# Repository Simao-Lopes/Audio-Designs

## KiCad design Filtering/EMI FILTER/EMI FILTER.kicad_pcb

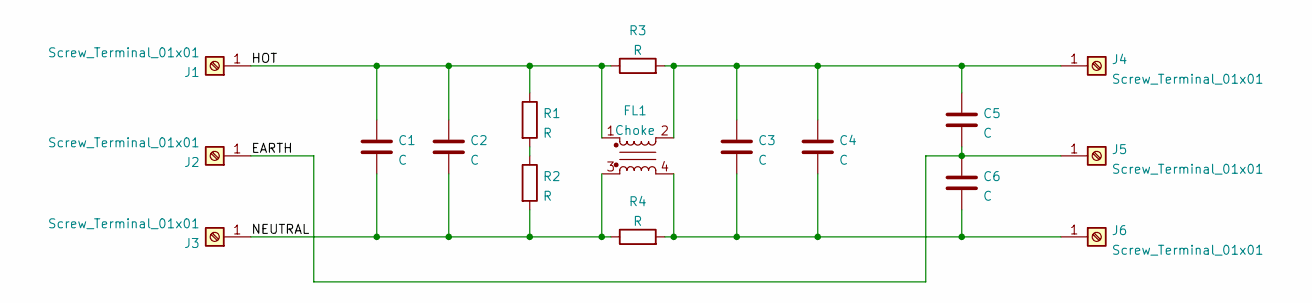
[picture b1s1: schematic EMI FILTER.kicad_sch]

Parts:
C1, C2, C3, C4: C; C_Rect_L31.5mm_W13.0mm_P27.50mm_MKS4
C5, C6: C; C_Rect_L13.0mm_W5.0mm_P10.00mm_FKS3_FKP3_MKS4
FL1: Choke; IND_CMT-8121
J1, J2, J3, J4, J5, J6: Screw_Terminal_01x01; M4_Screw_Terminal
R1, R2: R; R_Axial_DIN0207_L6.3mm_D2.5mm_P7.62mm_Horizontal
R3, R4: R; R_Axial_DIN0516_L15.5mm_D5.0mm_P20.32mm_Horizontal

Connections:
/EARTH: C5.2, C6.1, J2.1, J5.1
/HOT: C1.1, C2.1, FL1.1, J1.1, R1.1, R3.1; also elsewhere on the board
/NEUTRAL: C1.2, C2.2, FL1.3, J3.1, R2.2, R4.1; also elsewhere on the board
unnamed 3: C3.1, C4.1, C5.1, FL1.2, J4.1, R3.2; also elsewhere on the board
unnamed 4: C3.2, C4.2, C6.2, FL1.4, J6.1, R4.2; also elsewhere on the board
unnamed: R1.2, R2.1

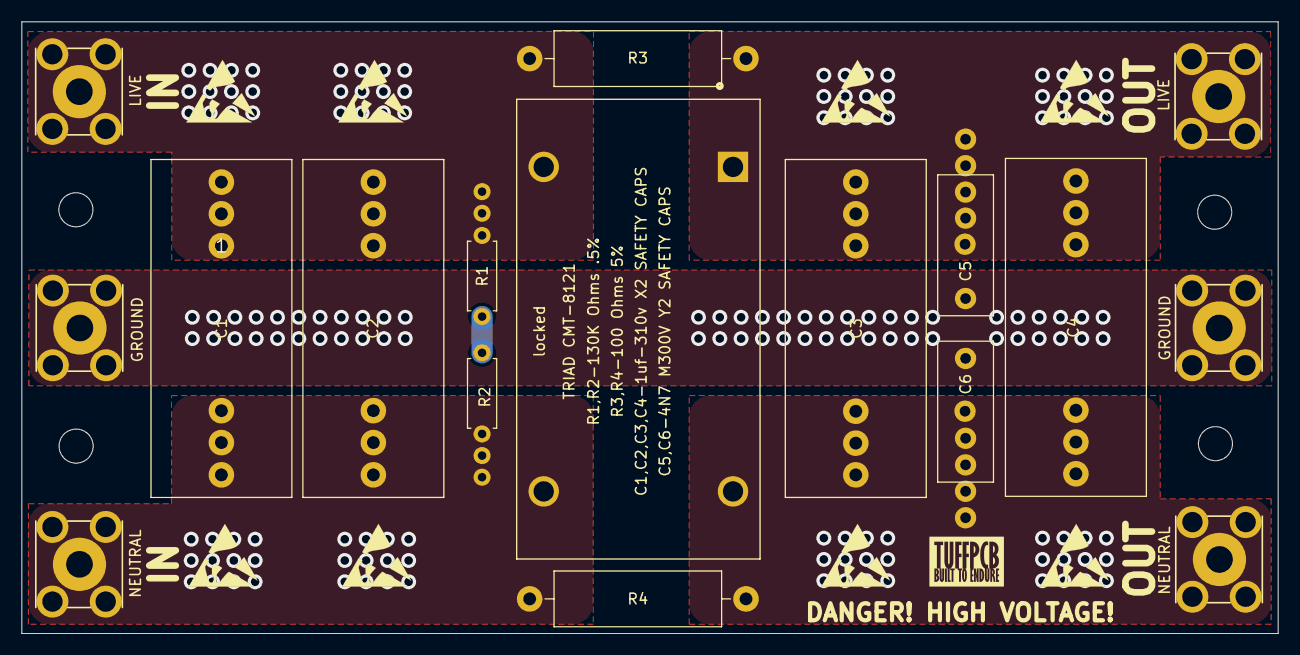
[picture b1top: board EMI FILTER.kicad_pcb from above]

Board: 2 copper layers, 118.0 x 57.5 mm, 18 parts (0 on the bottom side), 6 nets.

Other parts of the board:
1: (no value)
TRIAD CMT-8121: locked; IND_CMT-8121

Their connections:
/HOT: 1.1, TRIAD CMT-8121.1; also elsewhere on the board
/NEUTRAL: TRIAD CMT-8121.3; also elsewhere on the board
unnamed 3: TRIAD CMT-8121.2; also elsewhere on the board
unnamed 4: TRIAD CMT-8121.4; also elsewhere on the board

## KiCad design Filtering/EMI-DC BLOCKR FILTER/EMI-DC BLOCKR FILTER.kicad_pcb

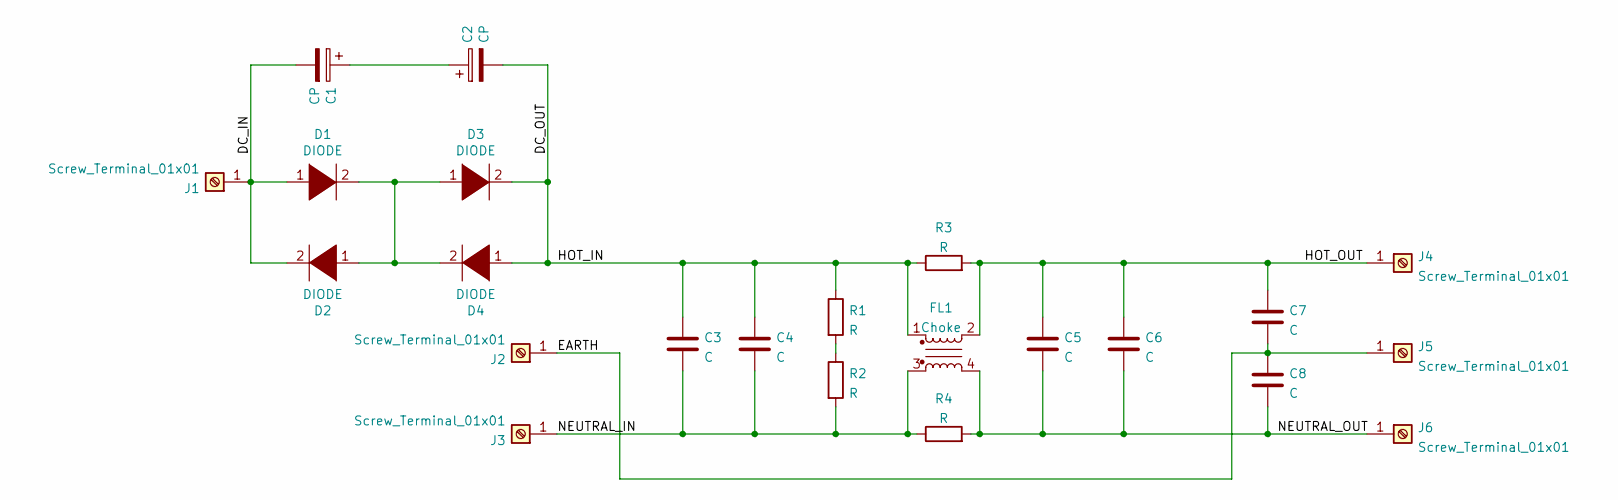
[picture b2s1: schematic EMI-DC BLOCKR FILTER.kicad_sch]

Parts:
C1, C2: CP; CP_Radial_D35.0mm_P10.00mm_SnapIn
C3, C4, C5, C6: C; C_Rect_L31.5mm_W13.0mm_P27.50mm_MKS4
C7, C8: C; C_Rect_L13.0mm_W5.0mm_P10.00mm_FKS3_FKP3_MKS4
D1, D2, D3, D4: DIODE; D_DO-15_P15.24mm_Horizontal
FL1: Choke; IND_CMT-8121
J1, J2, J3, J4, J5, J6: Screw_Terminal_01x01; M4_Screw_Terminal
R1, R2: R; R_Axial_DIN0207_L6.3mm_D2.5mm_P7.62mm_Horizontal
R3, R4: R; R_Axial_DIN0516_L15.5mm_D5.0mm_P20.32mm_Horizontal

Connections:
/DC_IN: C1.2, D1.1 (K), D2.2 (A), J1.1
/EARTH: C7.2, C8.1, J2.1, J5.1
/HOT_IN: C2.2, C3.1, C4.1, D3.2 (A), D4.1 (K), FL1.1, R1.1, R3.1
/HOT_OUT: C5.1, C6.1, C7.1, FL1.2, J4.1, R3.2
/NEUTRAL_IN: C3.2, C4.2, FL1.3, J3.1, R2.2, R4.1
/NEUTRAL_OUT: C5.2, C6.2, C8.2, FL1.4, J6.1, R4.2
unnamed: C1.1, C2.1
unnamed: D1.2 (A), D2.1 (K), D3.1 (K), D4.2 (A)
unnamed: R1.2, R2.1

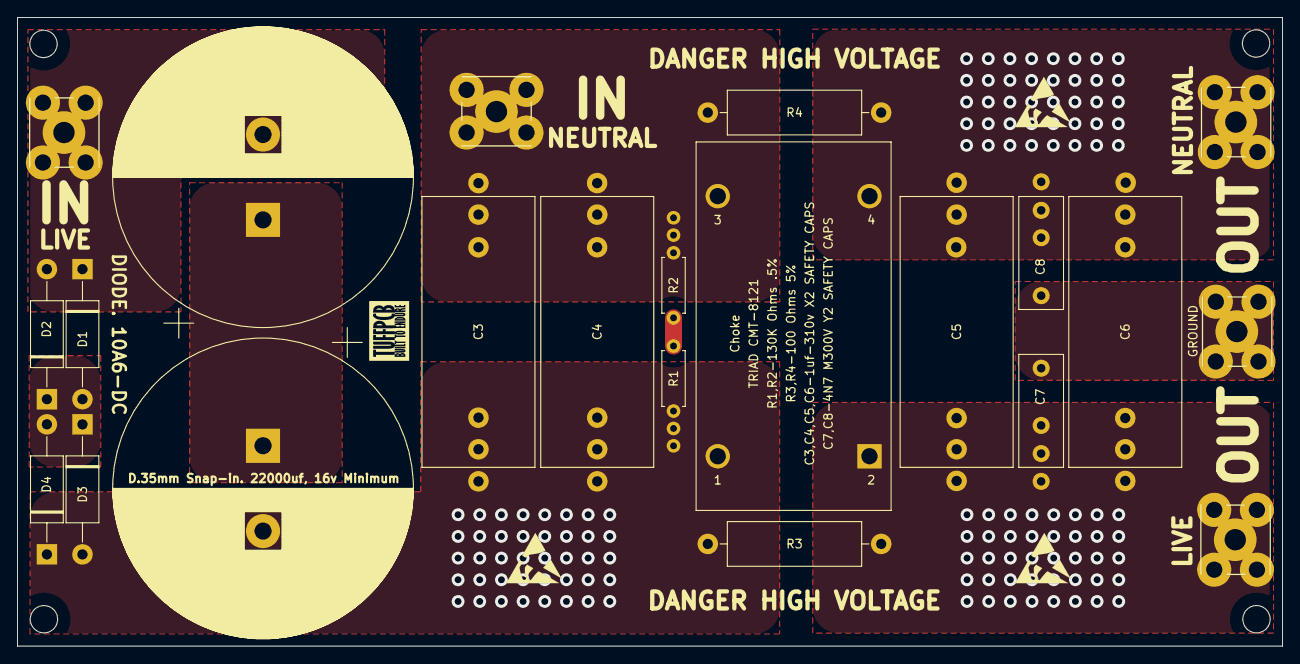
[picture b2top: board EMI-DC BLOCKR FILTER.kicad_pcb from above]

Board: 2 copper layers, 148.2 x 73.7 mm, 22 parts (1 on the bottom side), 9 nets.

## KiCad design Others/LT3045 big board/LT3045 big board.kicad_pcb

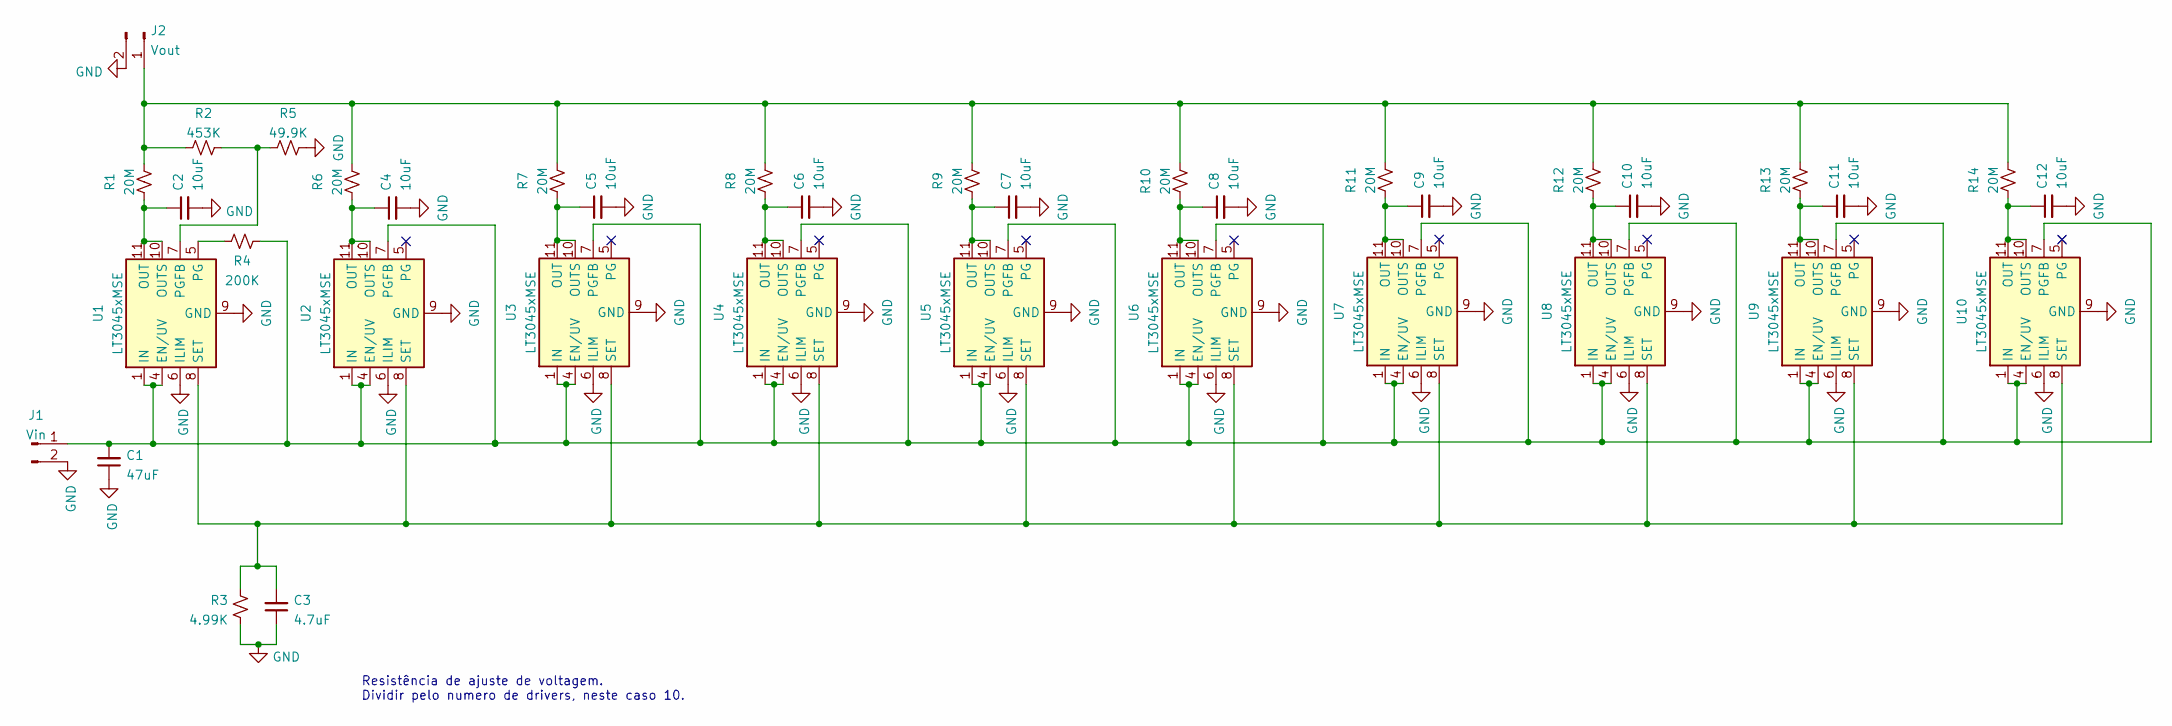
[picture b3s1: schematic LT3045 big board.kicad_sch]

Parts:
C1: 47uF; C_1210_3225Metric_Pad1.33x2.70mm_HandSolder
C2, C4, C5, C6, C7, C8, C9, C10, C11, C12: 10uF; C_1210_3225Metric_Pad1.33x2.70mm_HandSolder
C3: 4.7uF; C_1210_3225Metric_Pad1.33x2.70mm_HandSolder
J1: Vin; TerminalBlock_Altech_AK300-2_P5.00mm
J2: Vout; TerminalBlock_Altech_AK300-2_P5.00mm
R1, R6, R7, R8, R9, R10, R11, R12, R13, R14: 20M; R_1206_3216Metric_Pad1.30x1.75mm_HandSolder
R2: 453K; R_1206_3216Metric_Pad1.30x1.75mm_HandSolder
R3: 4.99K; R_1206_3216Metric_Pad1.30x1.75mm_HandSolder
R4: 200K; R_1206_3216Metric_Pad1.30x1.75mm_HandSolder
R5: 49.9K; R_1206_3216Metric_Pad1.30x1.75mm_HandSolder
U1, U2, U3, U4, U5, U6, U7, U8, U9, U10: LT3045xMSE; MSOP-12-1EP_3x4mm_P0.65mm_EP1.65x2.85mm

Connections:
GND: C1.1, C2.2, C3.1, C4.2, C5.2, C6.2, C7.2, C8.2, C9.2, C10.2, C11.2, C12.2, J1.2, J2.2, R3.1, R5.1, U1.6 (ILIM), U1.9 (GND), U1.13 (GND), U2.6 (ILIM), U2.9 (GND), U2.13 (GND), U3.6 (ILIM), U3.9 (GND), U3.13 (GND), U4.6 (ILIM), U4.9 (GND), U4.13 (GND), U5.6 (ILIM), U5.9 (GND), U5.13 (GND), U6.6 (ILIM), U6.9 (GND), U6.13 (GND), U7.6 (ILIM), U7.9 (GND), U7.13 (GND), U8.6 (ILIM), U8.9 (GND), U8.13 (GND), U9.6 (ILIM), U9.9 (GND), U9.13 (GND), U10.6 (ILIM), U10.9 (GND), U10.13 (GND)
unnamed: C1.2, J1.1, R4.2, U1.1 (IN), U1.2 (IN), U1.3 (IN), U1.4 (EN/UV), U2.1 (IN), U2.2 (IN), U2.3 (IN), U2.4 (EN/UV), U2.7 (PGFB), U3.1 (IN), U3.2 (IN), U3.3 (IN), U3.4 (EN/UV), U3.7 (PGFB), U4.1 (IN), U4.2 (IN), U4.3 (IN), U4.4 (EN/UV), U4.7 (PGFB), U5.1 (IN), U5.2 (IN), U5.3 (IN), U5.4 (EN/UV), U5.7 (PGFB), U6.1 (IN), U6.2 (IN), U6.3 (IN), U6.4 (EN/UV), U6.7 (PGFB), U7.1 (IN), U7.2 (IN), U7.3 (IN), U7.4 (EN/UV), U7.7 (PGFB), U8.1 (IN), U8.2 (IN), U8.3 (IN), U8.4 (EN/UV), U8.7 (PGFB), U9.1 (IN), U9.2 (IN), U9.3 (IN), U9.4 (EN/UV), U9.7 (PGFB), U10.1 (IN), U10.2 (IN), U10.3 (IN), U10.4 (EN/UV), U10.7 (PGFB)
unnamed: C2.1, R1.1, U1.10 (OUTS), U1.11 (OUT), U1.12 (OUT)
unnamed: C3.2, R3.2, U1.8 (SET), U2.8 (SET), U3.8 (SET), U4.8 (SET), U5.8 (SET), U6.8 (SET), U7.8 (SET), U8.8 (SET), U9.8 (SET), U10.8 (SET)
unnamed: C4.1, R6.1, U2.10 (OUTS), U2.11 (OUT), U2.12 (OUT)
unnamed: C5.1, R7.1, U3.10 (OUTS), U3.11 (OUT), U3.12 (OUT)
unnamed: C6.1, R8.1, U4.10 (OUTS), U4.11 (OUT), U4.12 (OUT)
unnamed: C7.1, R9.1, U5.10 (OUTS), U5.11 (OUT), U5.12 (OUT)
unnamed: C8.1, R10.1, U6.10 (OUTS), U6.11 (OUT), U6.12 (OUT)
unnamed: C9.1, R11.1, U7.10 (OUTS), U7.11 (OUT), U7.12 (OUT)
unnamed: C10.1, R12.1, U8.10 (OUTS), U8.11 (OUT), U8.12 (OUT)
unnamed: C11.1, R13.1, U9.10 (OUTS), U9.11 (OUT), U9.12 (OUT)
unnamed: C12.1, R14.1, U10.10 (OUTS), U10.11 (OUT), U10.12 (OUT)
unnamed: J2.1, R1.2, R2.2, R6.2, R7.2, R8.2, R9.2, R10.2, R11.2, R12.2, R13.2, R14.2
unnamed: R2.1, R5.2, U1.7 (PGFB)
unnamed: R4.1, U1.5 (PG)

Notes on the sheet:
Resistência de ajuste de voltagem. Dividir pelo numero de drivers, neste caso 10.

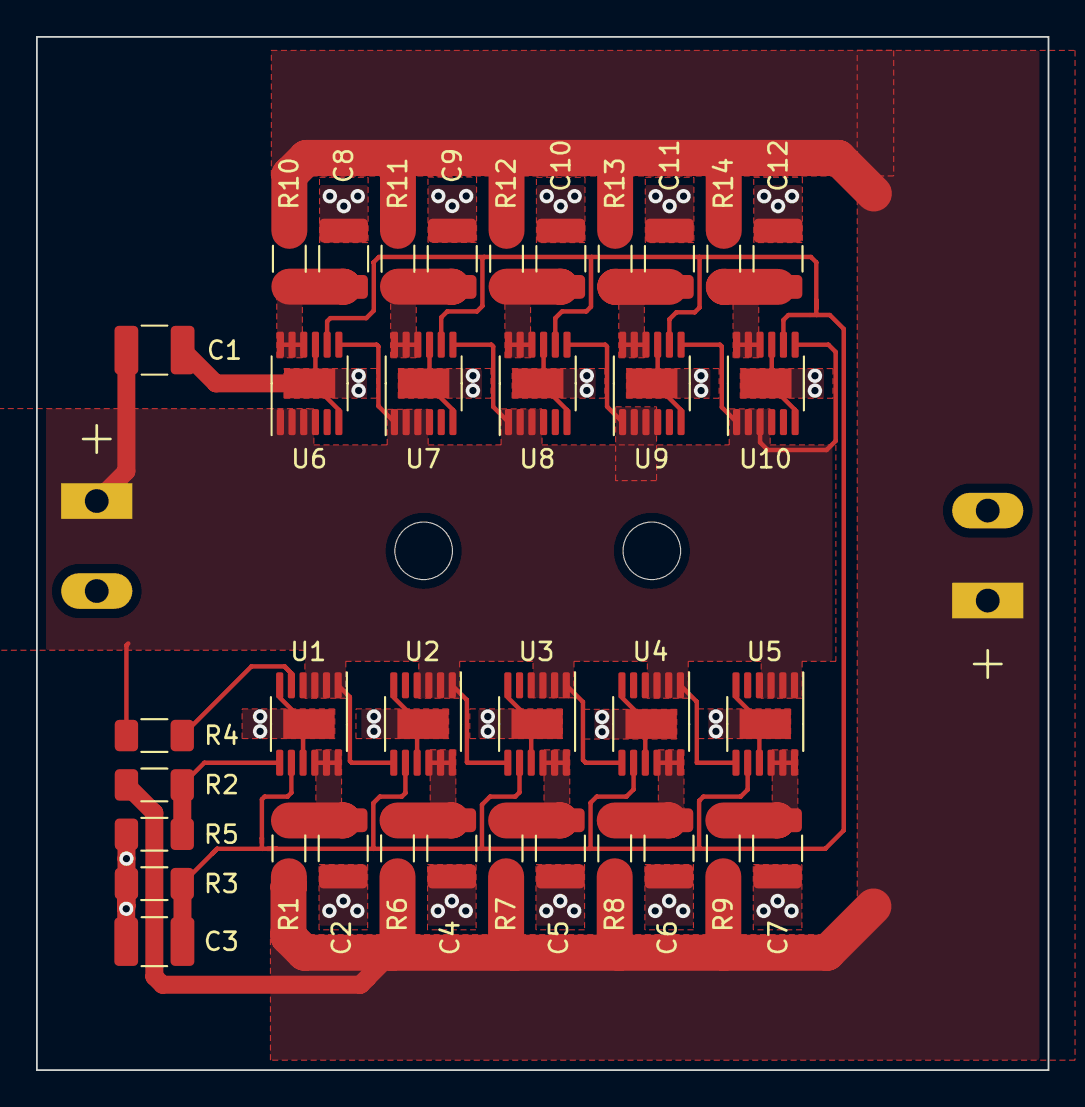
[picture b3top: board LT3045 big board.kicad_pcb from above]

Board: 2 copper layers, 56.2 x 57.4 mm, 38 parts (0 on the bottom side), 16 nets.

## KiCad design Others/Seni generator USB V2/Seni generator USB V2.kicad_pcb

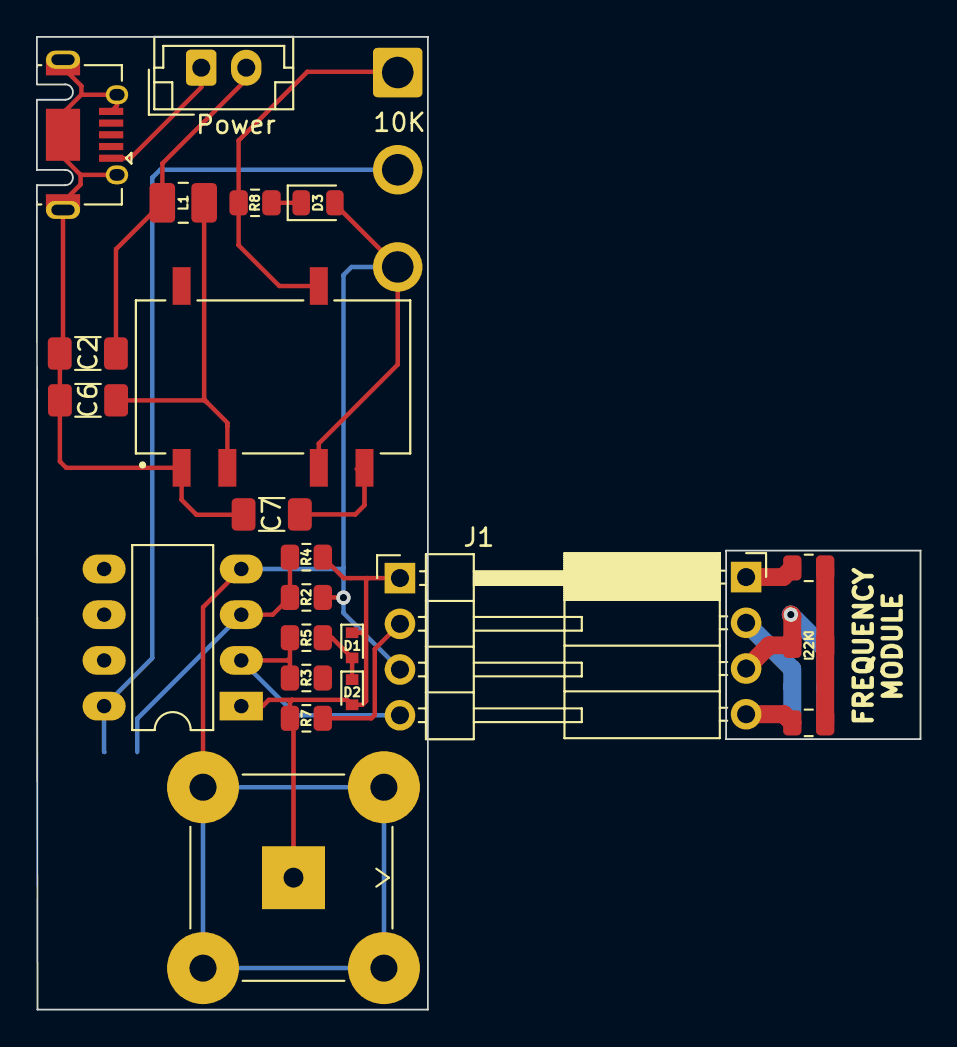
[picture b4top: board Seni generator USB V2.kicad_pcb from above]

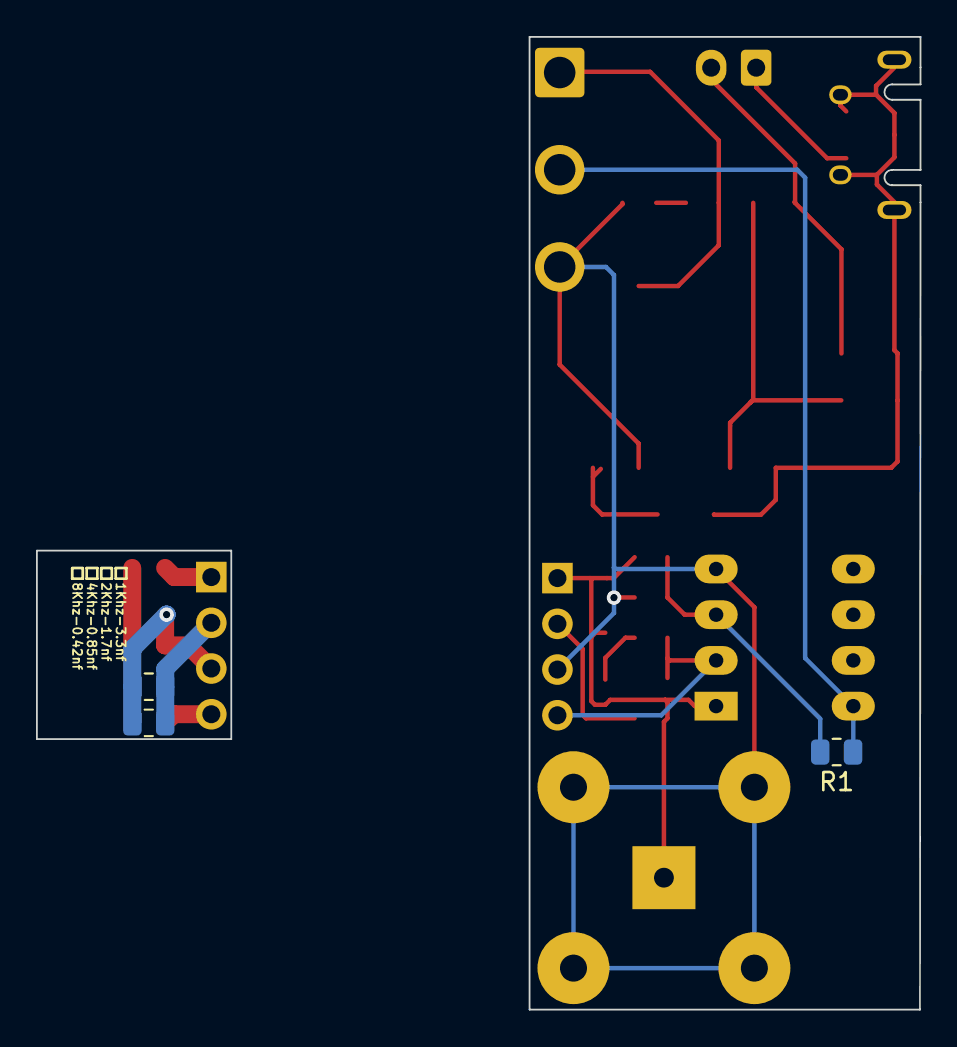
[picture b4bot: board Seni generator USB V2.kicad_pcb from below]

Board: 2 copper layers, 49.1 x 54.0 mm, 27 parts (3 on the bottom side), 19 nets.

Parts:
10K: 10K; SolderWire-1sqmm_1x03_P5.4mm_D1.4mm_OD2.7mm
22K: 22k; R_0805_2012Metric
C1, C3, C4, C5: 0.01uf; R_0805_2012Metric
C2, C6: 4u7; C_1206_3216Metric_Pad1.33x1.80mm_HandSolder
C7: 1nf/4kv; C_1206_3216Metric_Pad1.33x1.80mm_HandSolder
D1, D2: 1N4148; D_SOD-523
D3: LED; LED_0805_2012Metric
J1: Board In; PinHeader_1x04_P2.54mm_Horizontal
J2: Freq_board; PinSocket_1x04_P2.54mm_Horizontal
J3: Conn_Coaxial; BNC_TEConnectivity_1478035_Horizontal
J4: USB_B_Mini; USB_Micro-AB_Molex_47590-0001
L1: 6.8uh; L_1008_2520Metric_Pad1.43x2.20mm_HandSolder
Power: SW_DIP_x01; JST_EH_B2B-EH-A_1x02_P2.50mm_Vertical
R1, R2, R8: 10K; R_0805_2012Metric
R3: 47K; R_0805_2012Metric
R4: 300K; R_0805_2012Metric
R5: 470K; R_0805_2012Metric
R7: 47k; R_0805_2012Metric
U1: LM358; DIP-8_W7.62mm_LongPads
U2: PESE1-S5-D12-M; CONV_PESE1-S5-D12-M

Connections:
/Gnd_board: 22K.2, C1.1, C4.1, J2.3
GND: 10K.3, D3.2 (A), J1.3, J3.2 (Ext), R2.2, U1.4 (V-), U2.4 (0V)
unnamed: C1.2, C4.2, J2.2
unnamed: C2.2, C6.1, C7.1, J4.5 (GND), J4.6 (Shield), U2.1 (VIN-)
unnamed: C3.1, J2.4
unnamed: 22K.1, C3.2, C5.1
unnamed: C5.2, J2.1
unnamed: C6.2, L1.2, U2.2 (VIN+)
unnamed: C7.2, U2.5 (VOUT-)
unnamed: D1.1 (K), D2.2 (A), J1.1, J3.1 (In), R4.2, R7.2, U1.1
unnamed: D1.2 (A), D2.1 (K), R5.2
unnamed: D3.1 (K), R8.1
unnamed: J1.2, R3.2, R7.1
unnamed: J1.4, R3.1, R5.1, U1.2 (-)
unnamed: 10K.2, R1.1, U1.8 (V+)
unnamed: R1.2, R2.1, R4.1, U1.3 (+)
unnamed: 10K.1, R8.2, U2.7 (VOUT+)
unnamed: J4.1 (VBUS), Power.1
unnamed: C2.1, L1.1, Power.2

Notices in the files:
parts and their libraries:
Copyright 2016 Accelerated Designs. All rights reserved.
